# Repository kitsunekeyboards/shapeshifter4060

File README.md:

# shapeshifter4060
Home of the Shapeshifter 4060 keyboard

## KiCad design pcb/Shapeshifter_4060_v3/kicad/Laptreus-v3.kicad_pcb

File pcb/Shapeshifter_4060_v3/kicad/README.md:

# Kitsune Keyboards Shapeshifter 4060 v3.0

## PCB details

### Process reminders

#### Prepping for ordering from JLCPCB

1. File > Plot
- Format = Gerber
- Output directory = ../gerber/
- Included layers = Cu,Paste,SilkS,Mask,Edge.Cuts
2. Generate Drill Files
- Excellon
- Postscript
- Absolute origin
3. Open up GerbView from kicad
- File > Open Excellon Drill Files, select the two drl files (if you open these in the wrong order, the drill holes won't sit on top of the copper so it's hard to tell if there are any pads that aren't getting drilled)
- File > Open Gerber Files, select all the gbr files
- Hide all but the drill layers and F_Cu and B_Cu
- Stare and pretend that this means something to you
- Stare particularly hard at F_Cu and B_Cu
- Perhaps check to see if there are any lines that look like they're intersecting or something

#### Rotating the board so you can do wiring nicely

1. Show all layers
2. Select all with the mouse and rotate 10 degrees. To get the thumbs, rotate 40.
3. Hide Dwgs.User, set grid to 0.01mm, and "Set the origin point for the grid" to the center of the yellow cross on Eco2.User (center of the board about 10mm below the nice!nano)
4. Set the grid back to 0.1mm
5. Do some work

#### Setting up zones

1. Use the zone tool to draw a box around the area
2. Right click the zone (may have to select the board as well, then shift click it to deselect it) and Zones > Duplicate Zone to Layer
3. Press B to fill zones

#### Generating the BOM

1. Go into the schema editor
1. Tools > Edit Symbol Fields
1. Add the fields "Designation" and "Supplier Number"
1. Find your parts from the Elecrow parts library: https://www.elecrow.com/component-library.html?page=1&cate=Switch
1. Add the part number (like B3U-1000p) to the Supplier Number, and if there is one, add the pad shape (like SOD-123) to the Designation. Also add the Datasheet link.
1. Group by Supplier Number
1. Apply and then hit OK
1. Tools > Generate BOM
1. Choose `bom2grouped_csv` and Generate
1. `mv Laptreus-v3 ../bom/Laptreus-v3.csv`
1. `rm Laptreus-v3.xml`
1. Import `bom/Laptreus-v3.csv` to google drive (not sure why it doesn't have .csv on the end)
1. Copy all the switch References into VSCode and smash them onto one line, then replace the Reference on the first switch. Do the same for Values.
1. Now delete all the extra switches and clean up the rows
1. Now delete all the rows that represent things we don't want them assembling (nice nano for instance)
1. Copy all the values and past to VSCode, this should make a tsv. Save the file to `bom/Laptreus-v3.tsv`

#### Generate the position file

1. In PCBNew, File > Fabrication Outputs > Generate footprint position files
1. Set output path to `../pcba/`, ASCII, millimeters, Separate files for front and back

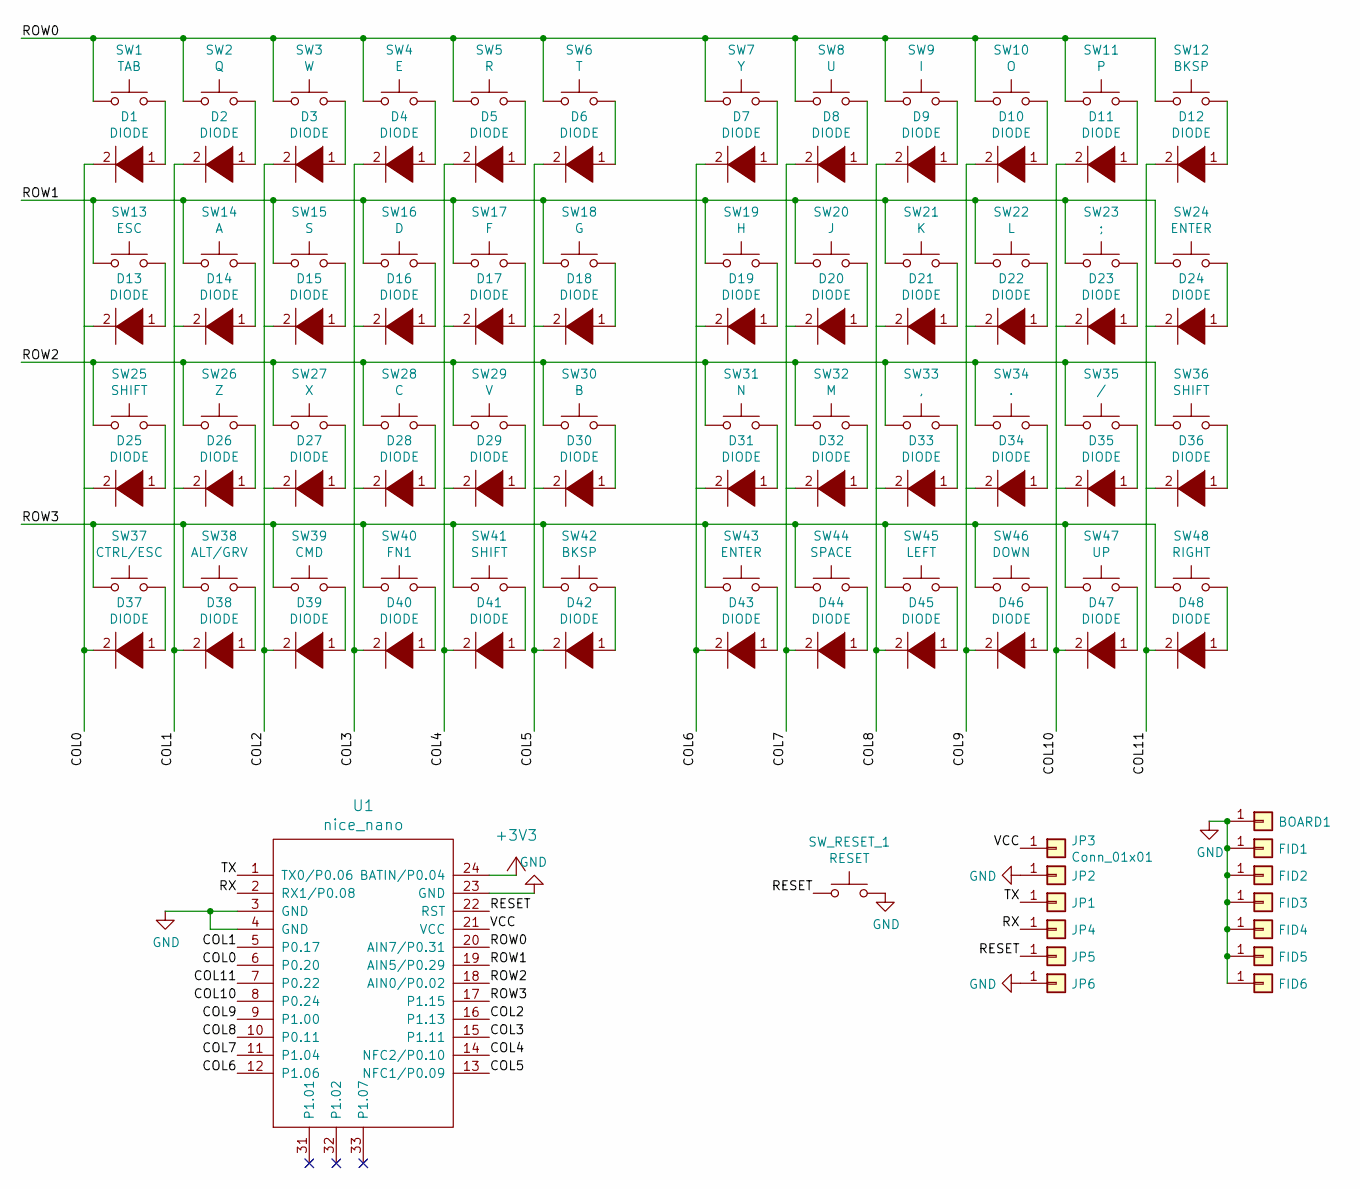
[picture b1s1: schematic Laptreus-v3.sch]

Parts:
BOARD1: Conn_01x01; 60_percent_plus_tofu_no_center_holes
D1, D2, D3, D4, D5, D6, D7, D8, D9, D10, D11, D12, D13, D14, D15, D16, D17, D18, D19, D20, D21, D22, D23, D24, D25, D26, D27, D28, D29, D30, D31, D32, D33, D34, D35, D36, D37, D38, D39, D40, D41, D42, D43, D44, D45, D46, D47, D48: DIODE; Diode-dual
FID1, FID2, FID3, FID4, FID5, FID6: Conn_01x01; FIDUCIAL
JP1, JP2, JP3, JP4, JP5, JP6: Conn_01x01; 1X01-CLEANBIG
SW1: TAB; Hybrid_Kailh_MX_Choc_Socket_Through_Hole_With_Diode
SW2: Q; Hybrid_Kailh_MX_Choc_Socket_Through_Hole_With_Diode
SW3: W; Hybrid_Kailh_MX_Choc_Socket_Through_Hole_With_Diode
SW4: E; Hybrid_Kailh_MX_Choc_Socket_Through_Hole_With_Diode
SW5: R; Hybrid_Kailh_MX_Choc_Socket_Through_Hole_With_Diode
SW6: T; Hybrid_Kailh_MX_Choc_Socket_Through_Hole_With_Diode
SW7: Y; Hybrid_Kailh_MX_Choc_Socket_Through_Hole_With_Diode
SW8: U; Hybrid_Kailh_MX_Choc_Socket_Through_Hole_With_Diode
SW9: I; Hybrid_Kailh_MX_Choc_Socket_Through_Hole_With_Diode
SW10: O; Hybrid_Kailh_MX_Choc_Socket_Through_Hole_With_Diode
SW11: P; Hybrid_Kailh_MX_Choc_Socket_Through_Hole_With_Diode
SW12, SW42: BKSP; Hybrid_Kailh_MX_Choc_Socket_Through_Hole_With_Diode
SW13: ESC; Hybrid_Kailh_MX_Choc_Socket_Through_Hole_With_Diode
SW14: A; Hybrid_Kailh_MX_Choc_Socket_Through_Hole_With_Diode_No_Diod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
SW15: S; Hybrid_Kailh_MX_Choc_Socket_Through_Hole_With_Diode
SW16: D; Hybrid_Kailh_MX_Choc_Socket_Through_Hole_With_Diode
SW17: F; Hybrid_Kailh_MX_Choc_Socket_Through_Hole_With_Diode
SW18: G; Hybrid_Kailh_MX_Choc_Socket_Through_Hole_With_Diode
SW19: H; Hybrid_Kailh_MX_Choc_Socket_Through_Hole_With_Diode
SW20: J; Hybrid_Kailh_MX_Choc_Socket_Through_Hole_With_Diode
SW21: K; Hybrid_Kailh_MX_Choc_Socket_Through_Hole_With_Diode
SW22: L; Hybrid_Kailh_MX_Choc_Socket_Through_Hole_With_Diode
SW23: ;; Hybrid_Kailh_MX_Choc_Socket_Through_Hole_With_Diode_No_Diod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
SW24: ENTER; Hybrid_Kailh_MX_Choc_Socket_Through_Hole_With_Diode_No_Diod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
SW25, SW36: SHIFT; Hybrid_Kailh_MX_Choc_Socket_Through_Hole_With_Diode_No_Diod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
SW26: Z; Hybrid_Kailh_MX_Choc_Socket_Through_Hole_With_Diode
SW27: X; Hybrid_Kailh_MX_Choc_Socket_Through_Hole_With_Diode
SW28: C; Hybrid_Kailh_MX_Choc_Socket_Through_Hole_With_Diode
SW29: V; Hybrid_Kailh_MX_Choc_Socket_Through_Hole_With_Diode
SW30: B; Hybrid_Kailh_MX_Choc_Socket_Through_Hole_With_Diode
SW31: N; Hybrid_Kailh_MX_Choc_Socket_Through_Hole_With_Diode
SW32: M; Hybrid_Kailh_MX_Choc_Socket_Through_Hole_With_Diode
SW33: ,; Hybrid_Kailh_MX_Choc_Socket_Through_Hole_With_Diode
SW34: .; Hybrid_Kailh_MX_Choc_Socket_Through_Hole_With_Diode
SW35: /; Hybrid_Kailh_MX_Choc_Socket_Through_Hole_With_Diode
SW37: CTRL/ESC; Hybrid_Kailh_MX_Choc_Socket_Through_Hole_With_Diode
SW38: ALT/GRV; Hybrid_Kailh_MX_Choc_Socket_Through_Hole_With_Diode
SW39: CMD; Hybrid_Kailh_MX_Choc_Socket_Through_Hole_With_Diode
SW40: FN1; Hybrid_Kailh_MX_Choc_Socket_Through_Hole_With_Diode
SW41: SHIFT; Hybrid_Kailh_MX_Choc_Socket_Through_Hole_With_Diode
SW43: ENTER; Hybrid_Kailh_MX_Choc_Socket_Through_Hole_With_Diode
SW44: SPACE; Hybrid_Kailh_MX_Choc_Socket_Through_Hole_With_Diode
SW45: LEFT; Hybrid_Kailh_MX_Choc_Socket_Through_Hole_With_Diode
SW46: DOWN; Hybrid_Kailh_MX_Choc_Socket_Through_Hole_With_Diode
SW47: UP; Hybrid_Kailh_MX_Choc_Socket_Through_Hole_With_Diode
SW48: RIGHT; Hybrid_Kailh_MX_Choc_Socket_Through_Hole_With_Diode
SW_RESET_1: RESET; SW_SPST_B3U-1000P
U1: nice_nano; nice_nano_no_Bcu_mask

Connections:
/COL0: D1.2 (A), D13.2 (A), D25.2 (A), D37.2 (A), U1.6 (P0.20)
/COL1: D2.2 (A), D14.2 (A), D26.2 (A), D38.2 (A), U1.5 (P0.17)
/COL2: D3.2 (A), D15.2 (A), D27.2 (A), D39.2 (A), U1.16 (P1.13)
/COL3: D4.2 (A), D16.2 (A), D28.2 (A), D40.2 (A), U1.15 (P1.11)
/COL4: D5.2 (A), D17.2 (A), D29.2 (A), D41.2 (A), U1.14 (NFC2/P0.10)
/COL5: D6.2 (A), D18.2 (A), D30.2 (A), D42.2 (A), U1.13 (NFC1/P0.09)
/COL6: D7.2 (A), D19.2 (A), D31.2 (A), D43.2 (A), U1.12 (P1.06)
/COL7: D8.2 (A), D20.2 (A), D32.2 (A), D44.2 (A), U1.11 (P1.04)
/COL8: D9.2 (A), D21.2 (A), D33.2 (A), D45.2 (A), U1.10 (P0.11)
/COL9: D10.2 (A), D22.2 (A), D34.2 (A), D46.2 (A), U1.9 (P1.00)
/COL10: D11.2 (A), D23.2 (A), D35.2 (A), D47.2 (A), U1.8 (P0.24)
/COL11: D12.2 (A), D24.2 (A), D36.2 (A), D48.2 (A), U1.7 (P0.22)
/RESET: JP5.1, SW_RESET_1.1, U1.22 (RST)
/ROW0: SW1.1, SW2.1, SW3.1, SW4.1, SW5.1, SW6.1, SW7.1, SW8.1, SW9.1, SW10.1, SW11.1, SW12.1, U1.20 (AIN7/P0.31)
/ROW1: SW13.1, SW14.1, SW15.1, SW16.1, SW17.1, SW18.1, SW19.1, SW20.1, SW21.1, SW22.1, SW23.1, SW24.1, U1.19 (AIN5/P0.29)
/ROW2: SW25.1, SW26.1, SW27.1, SW28.1, SW29.1, SW30.1, SW31.1, SW32.1, SW33.1, SW34.1, SW35.1, SW36.1, U1.18 (AIN0/P0.02)
/ROW3: SW37.1, SW38.1, SW39.1, SW40.1, SW41.1, SW42.1, SW43.1, SW44.1, SW45.1, SW46.1, SW47.1, SW48.1, U1.17 (P1.15)
/RX: JP4.1, U1.2 (RX1/P0.08)
/TX: JP1.1, U1.1 (TX0/P0.06)
/VCC: JP3.1, U1.21 (VCC)
GND: BOARD1.1, FID1.1, FID2.1, FID3.1, FID4.1, FID5.1, FID6.1, JP2.1, JP6.1, SW_RESET_1.2, U1.3 (GND), U1.4 (GND), U1.23 (GND)
unnamed: D1.1 (K), SW1.2
unnamed: D2.1 (K), SW2.2
unnamed: D3.1 (K), SW3.2
unnamed: D4.1 (K), SW4.2
unnamed: D5.1 (K), SW5.2
unnamed: D6.1 (K), SW6.2
unnamed: D7.1 (K), SW7.2
unnamed: D8.1 (K), SW8.2
unnamed: D9.1 (K), SW9.2
unnamed: D10.1 (K), SW10.2
unnamed: D11.1 (K), SW11.2
unnamed: D12.1 (K), SW12.2
unnamed: D13.1 (K), SW13.2
unnamed: D14.1 (K), SW14.2
unnamed: D15.1 (K), SW15.2
unnamed: D16.1 (K), SW16.2
unnamed: D17.1 (K), SW17.2
unnamed: D18.1 (K), SW18.2
unnamed: D19.1 (K), SW19.2
unnamed: D20.1 (K), SW20.2
unnamed: D21.1 (K), SW21.2
unnamed: D22.1 (K), SW22.2
unnamed: D23.1 (K), SW23.2
unnamed: D24.1 (K), SW24.2
unnamed: D25.1 (K), SW25.2
unnamed: D26.1 (K), SW26.2
unnamed: D27.1 (K), SW27.2
unnamed: D28.1 (K), SW28.2
unnamed: D29.1 (K), SW29.2
unnamed: D30.1 (K), SW30.2
unnamed: D31.1 (K), SW31.2
unnamed: D32.1 (K), SW32.2
unnamed: D33.1 (K), SW33.2
unnamed: D34.1 (K), SW34.2
unnamed: D35.1 (K), SW35.2
unnamed: D36.1 (K), SW36.2
unnamed: D37.1 (K), SW37.2
unnamed: D38.1 (K), SW38.2
unnamed: D39.1 (K), SW39.2
unnamed: D40.1 (K), SW40.2
unnamed: D41.1 (K), SW41.2
unnamed: D42.1 (K), SW42.2
unnamed: D43.1 (K), SW43.2
unnamed: D44.1 (K), SW44.2
unnamed: D45.1 (K), SW45.2
unnamed: D46.1 (K), SW46.2
unnamed: D47.1 (K), SW47.2
unnamed: D48.1 (K), SW48.2

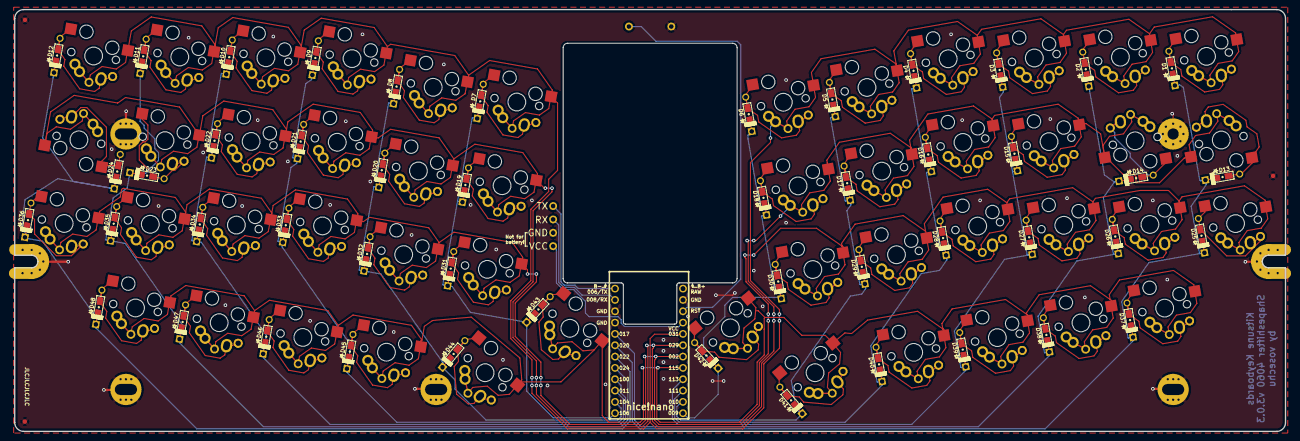
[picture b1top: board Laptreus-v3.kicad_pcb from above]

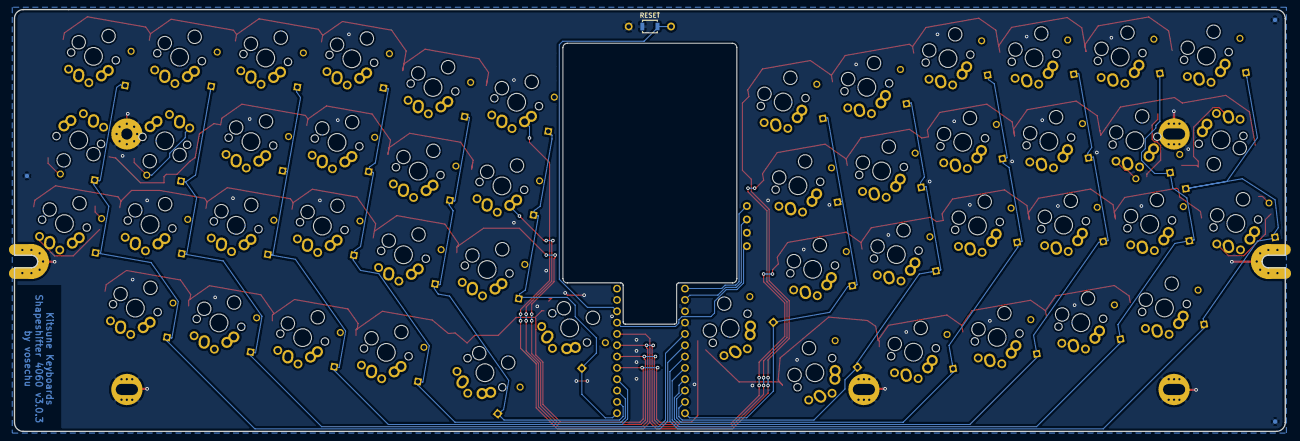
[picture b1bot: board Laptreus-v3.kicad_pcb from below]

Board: 2 copper layers, 285.0 x 94.6 mm, 111 parts (4 on the bottom side), 69 nets.

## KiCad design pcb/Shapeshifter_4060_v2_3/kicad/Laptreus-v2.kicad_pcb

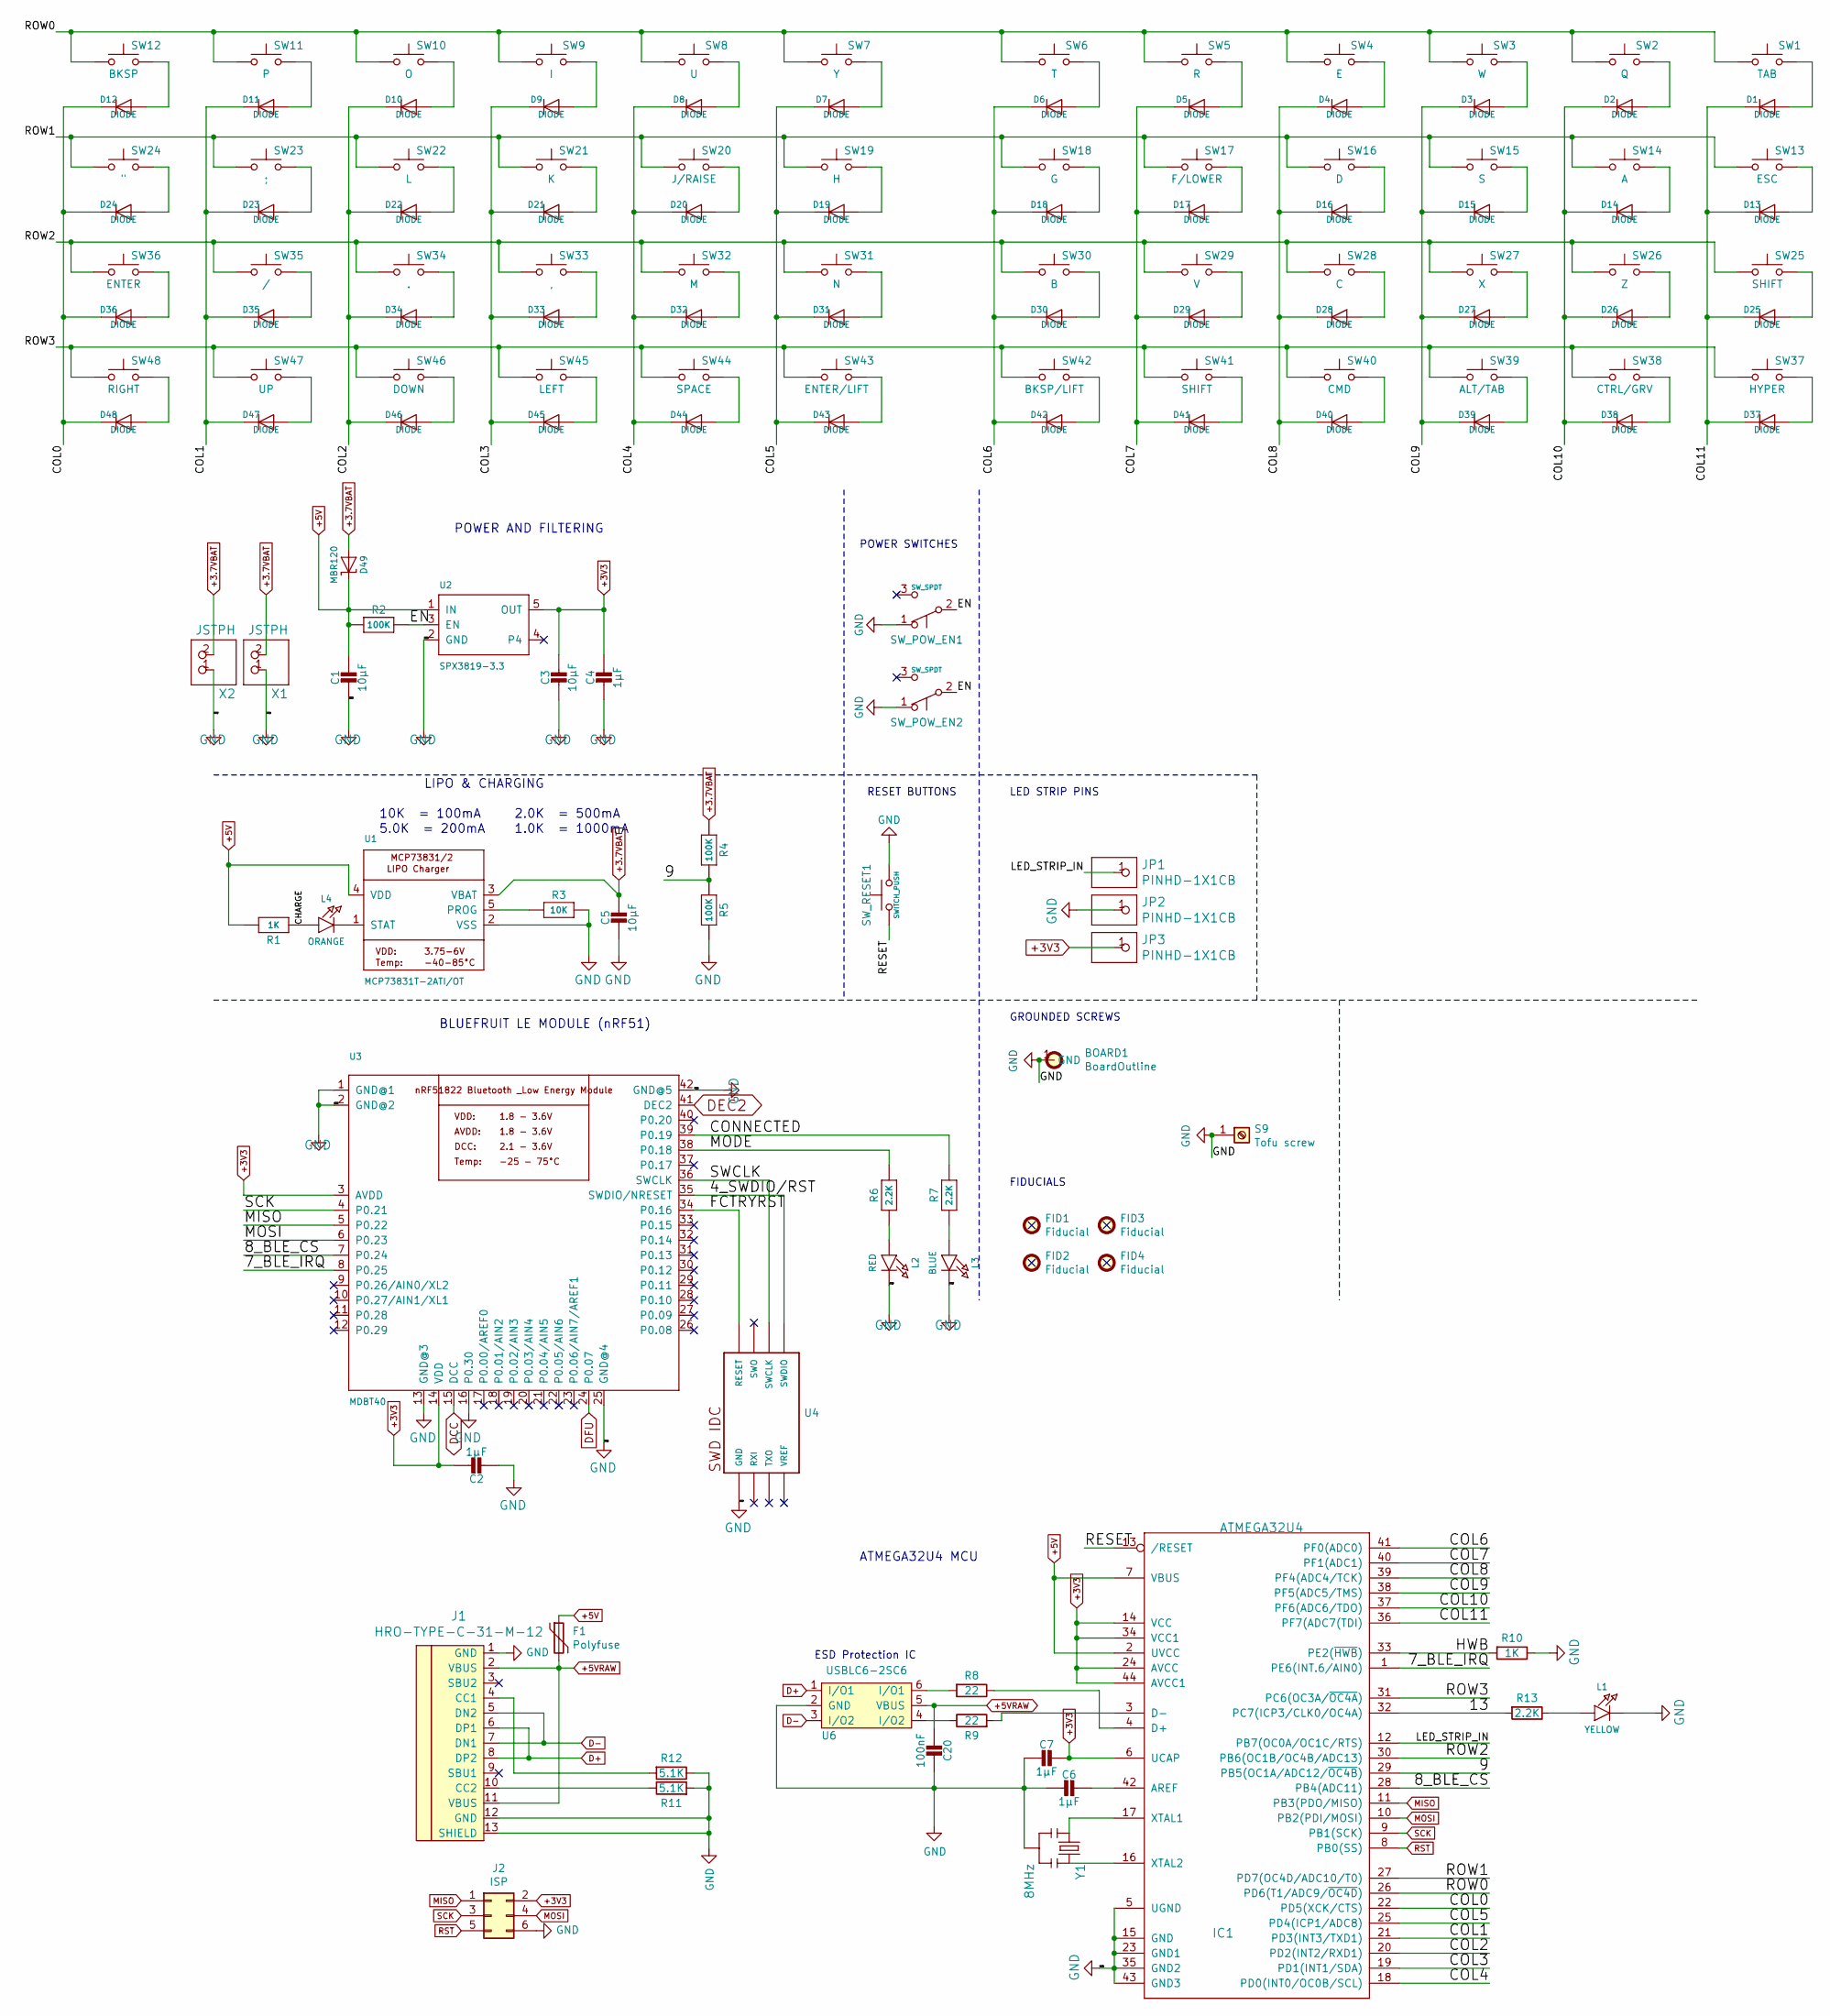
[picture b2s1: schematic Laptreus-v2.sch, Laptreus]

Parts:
BOARD1: BoardOutline; 60_percent_plus_tofu_no_center_holes
C1, C3, C5: 10µF; Capacitor_0805_MP; Manufacturer Part Number GRM21BR61A106KE19L; LCSC Part Number C77073
C2, C4, C6, C7: 1µF; Capacitor_0805_MP; Manufacturer Part Number GRM21BR71C105KA01L; LCSC Part Number C77079
C20: 100nF; Capacitor_0805_MP; Manufacturer Part Number GCM21BR72A104KA37L; LCSC Part Number C85866
D1, D2, D3, D4, D5, D6, D7, D8, D9, D10, D11, D12, D13, D14, D15, D16, D17, D18, D19, D20, D21, D22, D23, D24, D25, D26, D27, D28, D29, D30, D31, D32, D33, D34, D35, D36, D37, D38, D39, D40, D41, D42, D43, D44, D45, D46, D47, D48: DIODE; D_SOD-323_With_Test_Points; Manufacturer Part Number 1N4148W; LCSC Part Number C109203
D49: MBR120; D_SOD-323_With_Test_Points; Manufacturer Part Number MBR120LSF; LCSC Part Number C130880
F1: Polyfuse; Fuse_1812_4532Metric; Manufacturer Part Number 12H1200C; LCSC Part Number C182310
FID1, FID2, FID3, FID4: Fiducial; FIDUCIAL
IC1: ATMEGA32U4; TQFP-44_10x10mm_P0.8mm; Manufacturer Part Number ATMEGA32U4-AU; LCSC Part Number C44854
J1: HRO-TYPE-C-31-M-12; Manufacturer Part Number TYPE-C-31-M-13; LCSC Part Number C223906
J2: ISP; ISP_Standard
JP1, JP2, JP3: PINHD-1X1CB; 1X01-CLEANBIG
L1: YELLOW; LED_0603_1608Metric_Castellated; Manufacturer Part Number TJ-S2012SW8TGLC9Y-A5; LCSC Part Number C192671
L2: RED; LED_0603_1608Metric_Castellated; Manufacturer Part Number TJ-S2012SW8TGLC2R-A5; LCSC Part Number C192318
L3: BLUE; LED_0603_1608Metric_Castellated; Manufacturer Part Number TJ-S2012SW8TGLC6B-A5; LCSC Part Number C192320
L4: ORANGE; LED_0603_1608Metric_Castellated; Manufacturer Part Number TJ-S2012SW8TGLC0A-A5; LCSC Part Number C192670
R1, R10: 1K; R_0603_1608Metric; Manufacturer Part Number CR0805F81001G; LCSC Part Number C101404
R2, R4, R5: 100K; R_0603_1608Metric; Manufacturer Part Number CR0805F81003G; LCSC Part Number C101406
R3: 10K; R_0603_1608Metric; Manufacturer Part Number CR0805F81002G; LCSC Part Number C101405
R6, R7, R13: 2.2K; R_0603_1608Metric; Manufacturer Part Number CR0805F82201G; LCSC Part Number C101565
R8, R9: 22; R_0603_1608Metric; Manufacturer Part Number CR0805F822R0G; LCSC Part Number C101576
R11, R12: 5.1K; R_0603_1608Metric; Manufacturer Part Number CR0805F85101G; LCSC Part Number C101769
S9: Tofu screw; 5mm_M2.5_Screw_Hole_Plated
SW1: TAB; Kailh_Socket_With_Diode; Manufacturer Part Number CPG151101S11
SW2: Q; Kailh_Socket_With_Diode; Manufacturer Part Number CPG151101S11
SW3: W; Kailh_Socket_With_Diode; Manufacturer Part Number CPG151101S11
SW4: E; Kailh_Socket_With_Diode; Manufacturer Part Number CPG151101S11
SW5: R; Kailh_Socket_With_Diode; Manufacturer Part Number CPG151101S11
SW6: T; Kailh_Socket_With_Diode; Manufacturer Part Number CPG151101S11
SW7: Y; Kailh_Socket_With_Diode; Manufacturer Part Number CPG151101S11
SW8: U; Kailh_Socket_With_Diode; Manufacturer Part Number CPG151101S11
SW9: I; Kailh_Socket_With_Diode; Manufacturer Part Number CPG151101S11
SW10: O; Kailh_Socket_With_Diode; Manufacturer Part Number CPG151101S11
SW11: P; Kailh_Socket_With_Diode; Manufacturer Part Number CPG151101S11
SW12: BKSP; Kailh_Socket_With_Diode; Manufacturer Part Number CPG151101S11
SW13: ESC; Kailh_Socket_With_Diode; Manufacturer Part Number CPG151101S11
SW14: A; Kailh_Socket_With_Diode; Manufacturer Part Number CPG151101S11
SW15: S; Kailh_Socket_With_Diode; Manufacturer Part Number CPG151101S11
SW16: D; Kailh_Socket_With_Diode; Manufacturer Part Number CPG151101S11
SW17: F/LOWER; Kailh_Socket_With_Diode; Manufacturer Part Number CPG151101S11
SW18: G; Kailh_Socket_With_Diode; Manufacturer Part Number CPG151101S11
SW19: H; Kailh_Socket_With_Diode; Manufacturer Part Number CPG151101S11
SW20: J/RAISE; Kailh_Socket_With_Diode; Manufacturer Part Number CPG151101S11
SW21: K; Kailh_Socket_With_Diode; Manufacturer Part Number CPG151101S11
SW22: L; Kailh_Socket_With_Diode; Manufacturer Part Number CPG151101S11
SW23: ;; Kailh_Socket_With_Diode; Manufacturer Part Number CPG151101S11
SW24: \"; Kailh_Socket_With_Diode; Manufacturer Part Number CPG151101S11
SW25, SW41: SHIFT; Kailh_Socket_With_Diode; Manufacturer Part Number CPG151101S11
SW26: Z; Kailh_Socket_With_Diode; Manufacturer Part Number CPG151101S11
SW27: X; Kailh_Socket_With_Diode; Manufacturer Part Number CPG151101S11
SW28: C; Kailh_Socket_With_Diode; Manufacturer Part Number CPG151101S11
SW29: V; Kailh_Socket_With_Diode; Manufacturer Part Number CPG151101S11
SW30: B; Kailh_Socket_With_Diode; Manufacturer Part Number CPG151101S11
SW31: N; Kailh_Socket_With_Diode; Manufacturer Part Number CPG151101S11
SW32: M; Kailh_Socket_With_Diode; Manufacturer Part Number CPG151101S11
SW33: ,; Kailh_Socket_With_Diode; Manufacturer Part Number CPG151101S11
SW34: .; Kailh_Socket_With_Diode; Manufacturer Part Number CPG151101S11
SW35: /; Kailh_Socket_With_Diode; Manufacturer Part Number CPG151101S11
SW36: ENTER; Kailh_Socket_With_Diode; Manufacturer Part Number CPG151101S11
SW37: HYPER; Kailh_Socket_With_Diode; Manufacturer Part Number CPG151101S11
SW38: CTRL/GRV; Kailh_Socket_With_Diode; Manufacturer Part Number CPG151101S11
SW39: ALT/TAB; Kailh_Socket_With_Diode; Manufacturer Part Number CPG151101S11
SW40: CMD; Kailh_Socket_With_Diode; Manufacturer Part Number CPG151101S11
SW42: BKSP/LIFT; Kailh_Socket_With_Diode; Manufacturer Part Number CPG151101S11
SW43: ENTER/LIFT; Kailh_Socket_With_Diode; Manufacturer Part Number CPG151101S11
SW44: SPACE; Kailh_Socket_With_Diode; Manufacturer Part Number CPG151101S11
SW45: LEFT; Kailh_Socket_With_Diode; Manufacturer Part Number CPG151101S11
SW46: DOWN; Kailh_Socket_With_Diode; Manufacturer Part Number CPG151101S11
SW47: UP; Kailh_Socket_With_Diode; Manufacturer Part Number CPG151101S11
SW48: RIGHT; Kailh_Socket_With_Diode; Manufacturer Part Number CPG151101S11
SW_POW_EN1, SW_POW_EN2: SW_SPDT; EG1218; Manufacturer Part Number EG1218; LCSC Part Number C273394
SW_RESET1: SWITCH_PUSH; SW_SPST_B3U-1000P; Manufacturer Part Number B3U-1000P; LCSC Part Number C231329
U1: MCP73831T-2ATI/OT; SOT-23-5; Manufacturer Part Number MCP73831T-2ATI/OT; LCSC Part Number C14879
U2: SPX3819-3.3; SOT-23-5; Manufacturer Part Number SPX3819M5-L-3-3/TR; LCSC Part Number C9055
U3: MDBT40; BLE_MODULE_RAYTAC_MDBT40; Manufacturer Part Number MDBT40
U4: ARM-JTAG-SWD; ARM-JTAG-10-SWD-IDC
U6: USBLC6-2SC6; SOT-23-6; Manufacturer Part Number USBLC6-2SC6; Farnell 1295310
X1, X2: JSTPH; JSTPH2_With_THT; Manufacturer Part Number A2001WR-S-2P; LCSC Part Number C375128
Y1: 8MHz; 3_Pin_SMD_Resonator; Manufacturer Part Number CSTCE8M00G15C99-R0; LCSC Part Number C110614

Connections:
+3.7VBAT: C5.1, D49.1, D49.A, R4.1, U1.3 (VBAT), X1.2, X2.2
+3V3: C2.1, C3.1, C4.1, C7.1, IC1.6 (UCAP), IC1.14 (VCC), IC1.24 (AVCC), IC1.34 (VCC1), IC1.44 (AVCC1), J2.2, JP3.1, U2.5 (OUT), U3.3 (AVDD), U3.14 (VDD)
+5V: C1.1, D49.2, D49.C, F1.1, IC1.2 (UVCC), IC1.7 (VBUS), R1.2, R2.1, U1.4 (VDD), U2.1 (IN)
+5VRAW: C20.2, F1.2, J1.2 (VBUS), J1.11 (VBUS), U6.5 (VBUS)
/4_SWDIO/RST: U3.35 (SWDIO/NRESET), U4.SWDIO
/7_BLE_IRQ: IC1.1 (PE6(INT.6/AIN0)), U3.8 (P0.25)
/8_BLE_CS: IC1.28 (PB4(ADC11)), U3.7 (P0.24)
/9: IC1.29 (PB5(OC1A/ADC12/~OC4B)), R4.2, R5.1
/13: IC1.32 (PC7(ICP3/CLK0/OC4A)), R13.2
/CHARGE: L4.A, R1.1
/COL0: D12.1 (K), D24.1 (K), D36.1 (K), D48.1 (K), IC1.22 (PD5(XCK/CTS))
/COL1: D11.1 (K), D23.1 (K), D35.1 (K), D47.1 (K), IC1.21 (PD3(INT3/TXD1))
/COL2: D10.1 (K), D22.1 (K), D34.1 (K), D46.1 (K), IC1.20 (PD2(INT2/RXD1))
/COL3: D9.1 (K), D21.1 (K), D33.1 (K), D45.1 (K), IC1.19 (PD1(INT1/SDA))
/COL4: D8.1 (K), D20.1 (K), D32.1 (K), D44.1 (K), IC1.18 (PD0(INT0/OC0B/SCL))
/COL5: D7.1 (K), D19.1 (K), D31.1 (K), D43.1 (K), IC1.25 (PD4(ICP1/ADC8))
/COL6: D6.1 (K), D18.1 (K), D30.1 (K), D42.1 (K), IC1.41 (PF0(ADC0))
/COL7: D5.1 (K), D17.1 (K), D29.1 (K), D41.1 (K), IC1.40 (PF1(ADC1))
/COL8: D4.1 (K), D16.1 (K), D28.1 (K), D40.1 (K), IC1.39 (PF4(ADC4/TCK))
/COL9: D3.1 (K), D15.1 (K), D27.1 (K), D39.1 (K), IC1.38 (PF5(ADC5/TMS))
/COL10: D2.1 (K), D14.1 (K), D26.1 (K), D38.1 (K), IC1.37 (PF6(ADC6/TDO))
/COL11: D1.1 (K), D13.1 (K), D25.1 (K), D37.1 (K), IC1.36 (PF7(ADC7(TDI))
/CONNECTED: R7.2, U3.39 (P0.19)
/EN: R2.2, SW_POW_EN1.2 (B), SW_POW_EN2.2 (B), U2.3 (EN)
/FCTRYRST: U3.34 (P0.16), U4.RESET
/HWB: IC1.33 (PE2(~HWB)), R10.2
/LED_STRIP_IN: IC1.12 (PB7(OC0A/OC1C/RTS)), JP1.1
/MODE: R6.2, U3.38 (P0.18)
/RESET: IC1.13 (/RESET), SW_RESET1.1
/ROW0: IC1.26 (PD6(T1/ADC9/~OC4D)), SW1.1, SW2.1, SW3.1, SW4.1, SW5.1, SW6.1, SW7.1, SW8.1, SW9.1, SW10.1, SW11.1, SW12.1
/ROW1: IC1.27 (PD7(OC4D/ADC10/T0)), SW13.1, SW14.1, SW15.1, SW16.1, SW17.1, SW18.1, SW19.1, SW20.1, SW21.1, SW22.1, SW23.1, SW24.1
/ROW2: IC1.30 (PB6(OC1B/OC4B/ADC13)), SW25.1, SW26.1, SW27.1, SW28.1, SW29.1, SW30.1, SW31.1, SW32.1, SW33.1, SW34.1, SW35.1, SW36.1
/ROW3: IC1.31 (PC6(OC3A/~OC4A)), SW37.1, SW38.1, SW39.1, SW40.1, SW41.1, SW42.1, SW43.1, SW44.1, SW45.1, SW46.1, SW47.1, SW48.1
/SWCLK: U3.36 (SWCLK), U4.SWCLK
D+: J1.6 (DP1), J1.8 (DP2), U6.1 (I/O1)
D-: J1.5 (DN2), J1.7 (DN1), U6.3 (I/O2)
GND: BOARD1.1, C1.2, C2.2, C3.2, C4.2, C5.2, C6.2, C7.2, C20.1, IC1.5 (UGND), IC1.15 (GND), IC1.23 (GND1), IC1.35 (GND2), IC1.43 (GND3), J1.1 (GND), J1.12 (GND), J1.13 (SHIELD), J2.6, JP2.1, L1.C, L2.C, L3.C, R3.2, R5.2, R10.1, R11.2, R12.1, S9.1, SW_POW_EN1.1 (A), SW_POW_EN2.1 (A), SW_RESET1.2, U1.2 (VSS), U2.2 (GND), U3.1 (GND@1), U3.2 (GND@2), U3.13 (GND@3), U3.16 (P0.30), U3.25 (GND@4), U3.42 (GND@5), U4.GND@1 (GND), U4.GND@2 (GND), U4.GND@3 (GND), U6.2 (GND), X1.1, X2.1, Y1.2
MISO: IC1.11 (PB3(PDO/MISO)), J2.1, U3.5 (P0.22)
MOSI: IC1.10 (PB2(PDI/MOSI)), J2.4, U3.6 (P0.23)
unnamed: C6.1, IC1.42 (AREF)
unnamed: D1.2 (A), SW1.2
unnamed: D2.2 (A), SW2.2
unnamed: D3.2 (A), SW3.2
unnamed: D4.2 (A), SW4.2
unnamed: D5.2 (A), SW5.2
unnamed: D6.2 (A), SW6.2
unnamed: D7.2 (A), SW7.2
unnamed: D8.2 (A), SW8.2
unnamed: D9.2 (A), SW9.2
unnamed: D10.2 (A), SW10.2
unnamed: D11.2 (A), SW11.2
unnamed: D12.2 (A), SW12.2
unnamed: D13.2 (A), SW13.2
unnamed: D14.2 (A), SW14.2
unnamed: D15.2 (A), SW15.2
unnamed: D16.2 (A), SW16.2
unnamed: D17.2 (A), SW17.2
unnamed: D18.2 (A), SW18.2
unnamed: D19.2 (A), SW19.2
unnamed: D20.2 (A), SW20.2
unnamed: D21.2 (A), SW21.2
unnamed: D22.2 (A), SW22.2
unnamed: D23.2 (A), SW23.2
unnamed: D24.2 (A), SW24.2
unnamed: D25.2 (A), SW25.2
unnamed: D26.2 (A), SW26.2
unnamed: D27.2 (A), SW27.2
unnamed: D28.2 (A), SW28.2
unnamed: D29.2 (A), SW29.2
unnamed: D30.2 (A), SW30.2
unnamed: D31.2 (A), SW31.2
unnamed: D32.2 (A), SW32.2
unnamed: D33.2 (A), SW33.2
unnamed: D34.2 (A), SW34.2
unnamed: D35.2 (A), SW35.2
unnamed: D36.2 (A), SW36.2
unnamed: D37.2 (A), SW37.2
unnamed: D38.2 (A), SW38.2
unnamed: D39.2 (A), SW39.2
unnamed: D40.2 (A), SW40.2
unnamed: D41.2 (A), SW41.2
unnamed: D42.2 (A), SW42.2
unnamed: D43.2 (A), SW43.2
unnamed: D44.2 (A), SW44.2
unnamed: D45.2 (A), SW45.2
unnamed: D46.2 (A), SW46.2
unnamed: D47.2 (A), SW47.2
unnamed: D48.2 (A), SW48.2
unnamed: IC1.3 (D-), R9.2
unnamed: IC1.4 (D+), R8.1
unnamed: IC1.16 (XTAL2), Y1.3
unnamed: IC1.17 (XTAL1), Y1.1
unnamed: J1.4 (CC1), R12.2
unnamed: J1.10 (CC2), R11.1
unnamed: L1.A, R13.1
unnamed: L2.A, R6.1
unnamed: L3.A, R7.1
unnamed: L4.C, U1.1 (STAT)
unnamed: R3.1, U1.5 (PROG)
unnamed: R8.2, U6.6 (I/O1)
unnamed: R9.1, U6.4 (I/O2)
RST: IC1.8 (PB0(SS)), J2.5
SCK: IC1.9 (PB1(SCK)), J2.3, U3.4 (P0.21)

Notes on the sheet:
LIPO & CHARGING
1.0K = 1000mA
2.0K = 500mA
5.0K = 200mA
10K = 100mA
ATMEGA32U4 MCU
BLUEFRUIT LE MODULE (nRF51)
POWER AND FILTERING
RESET BUTTONS
POWER SWITCHES
ESD Protection IC
LED STRIP PINS
GROUNDED SCREWS
FIDUCIALS

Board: 4 copper layers, 146 parts (16 on the bottom side), 103 nets, no tracks yet.

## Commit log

2020-02-16 Move files from megarepo
2020-02-21 update shapeshifter to use newer components from non-ble library, move mdbt40
2020-02-23 try to move all footprints into library. Need to do symbols still
2020-02-29 starting redesign of shapeshifter wireless case
2020-02-29 Add pcb export to case to check dimensions
2021-08-11 Move a bunch of things to an archive folder
2021-08-11 Move footprints to a common area and symlink
2021-08-11 Not sure, backups maybe?
2021-08-11 Prep for v3
2021-08-11 Moving archive folder out of v2.3 and up to the pcbs directory
2021-08-11 Import footprints from other versions of the laptreus
2021-08-11 Update footprints for all objects on the PCB and annotate schema
2021-08-11 Update schema annotations to be correct and label each switch
2021-08-11 Update diode positions on the pcb
2021-08-11 Finished moving Diodes around
2021-08-13 added fids/jumpers to schematic, fixed wiring typo, added pro micro fo otprint
2021-08-13 Add nomask variant of nice nano, remove adhesives, add reset switch
2021-08-13 Add backups folder
2021-08-13 all components wired up!
2021-08-13 Adding backup for switches all wired in place
2021-08-13 Move reminders to a readme
2021-08-13 Finished board. Wow. So much faster this time...
2021-08-13 Adding backup of v3.0
2021-08-13 Finished and sent to JLCPCB
2021-08-15 Add pins for reset, add gerbers from last order, enlarged battery box
2021-08-15 enlarge the flipped arduino hole
2021-08-16 New revision with larger cutout for flipped pro micros
2021-08-24 Moved nice nano down, increased battery hole size
2021-09-10 Flip reset text, flip nicenano masks
2021-09-10 Add BOM/pos files for pcba

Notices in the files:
pcb/Shapeshifter_4060_v2_3/kicad/Laptreus-v2.sch:
https://creativecommons.org/licenses/by-sa/4.0
Released under Creative Commons
